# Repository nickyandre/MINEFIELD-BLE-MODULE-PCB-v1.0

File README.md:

# MINEFIELD-BLE-MODULE-PCB-v1.0
This repository is for MINEFIELD BLE Module PCB v1.0 which consist of NRF52840 BLE chip and BME280 temperature, humidity, and air pressure sensor. <br />

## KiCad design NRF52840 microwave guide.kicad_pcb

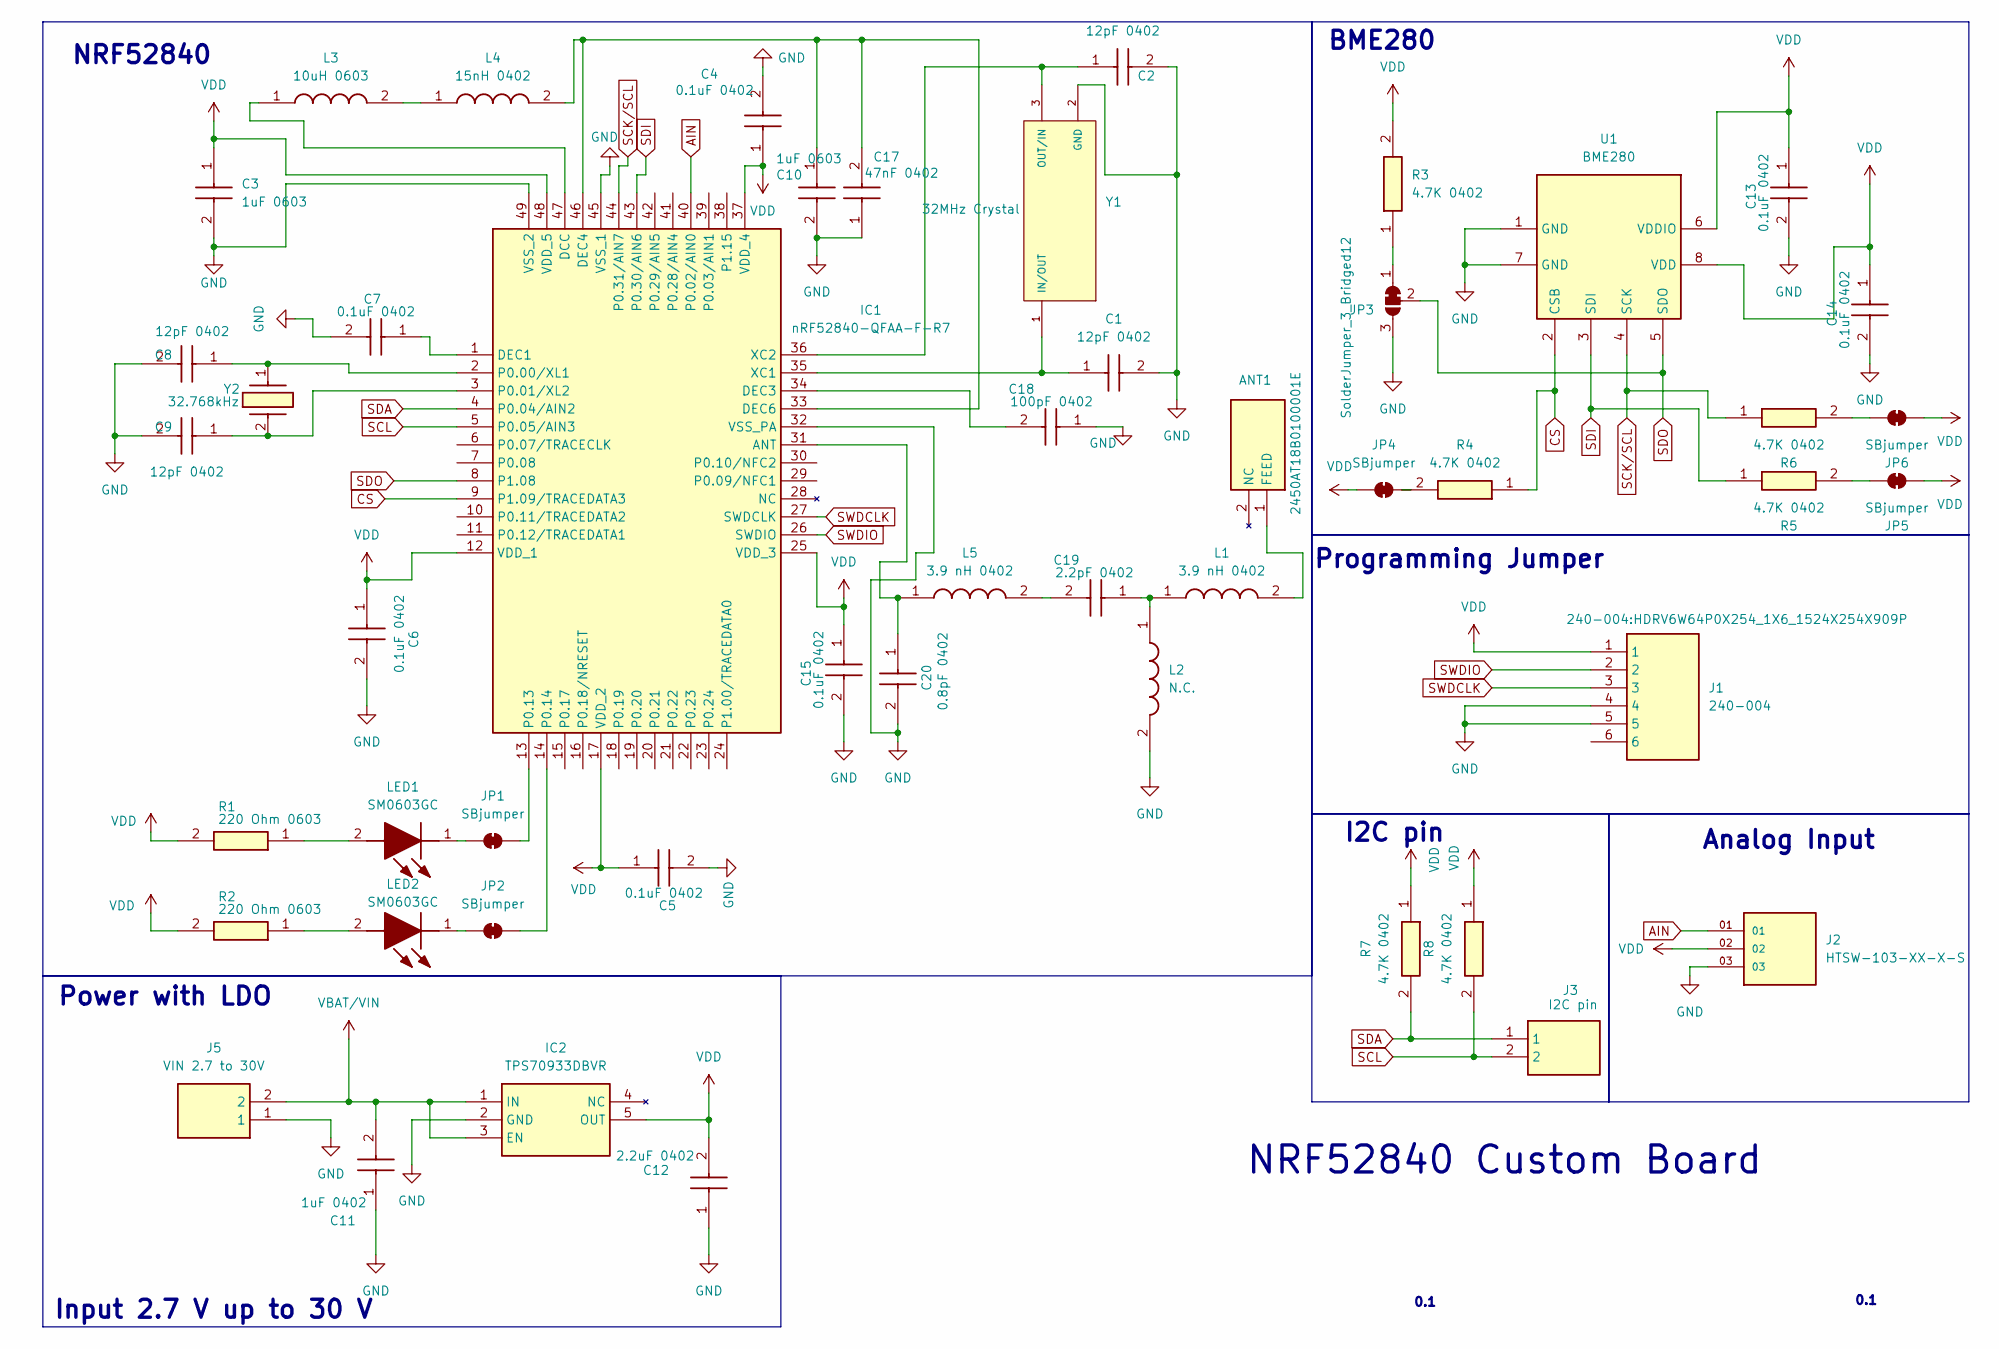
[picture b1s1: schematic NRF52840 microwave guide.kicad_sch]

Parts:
ANT1: 2450AT18B0100001E; ANTC3216X140N; Manufacturer_Part_Number 2450AT18B0100001E
C1, C2, C8, C9: 12pF 0402; 0402cap; Mouser Part Number 81-GRM1555C1H120GA1J
C3, C10: 1uF 0603; CAPC1608X90N; Manufacturer_Part_Number 06035C4R7KAT2A
C4, C5, C6, C7, C13, C14, C15: 0.1uF 0402; 0402cap; Mouser Part Number 81-GRM1555C1H120GA1J
C11: 1uF 0402; 0402cap; Mouser Part Number 81-GRM1555C1H120GA1J
C12: 2.2uF 0402; 0402cap; Mouser Part Number 81-GRM1555C1H120GA1J
C17: 47nF 0402; 0402cap; Mouser Part Number 81-GRM1555C1H120GA1J
C18: 100pF 0402; 0402cap; Mouser Part Number 81-GRM1555C1H120GA1J
C19: 2.2pF 0402; 0402cap; Mouser Part Number 81-GRM1555C1H120GA1J
C20: 0.8pF 0402; 0402cap; Mouser Part Number 81-GRM1555C1H120GA1J
IC1: nRF52840-QFAA-F-R7; QFN40P600X600X95-49N-D; Mouser Part Number 949-NRF52840QFAAF-R7
IC2: TPS70933DBVR; SOT95P280X145-5N; Mouser Part Number 595-TPS70933DBVR
J1: 240-004; HDRV6W64P0X254_1X6_1524X254X909P; Manufacturer_Part_Number 240-004
J2: HTSW-103-XX-X-S; SAMTEC_HTSW-103-XX-X-S; PARTREV B
J3: I2C pin; HDRV2W64P0X254_1X2_508X248X838P; Mouser Part Number 200-HTSW10208GS
J5: VIN 2.7 to 30V; HDRV2W64P0X254_1X2_508X248X838P; Mouser Part Number 200-HTSW10208GS
JP1, JP2, JP4, JP5, JP6: SBjumper; SolderJumper-2_P1.3mm_Bridged_RoundedPad1.0x1.5mm
JP3: SolderJumper_3_Bridged12; SolderJumper-3_P1.3mm_Bridged12_RoundedPad1.0x1.5mm_NumberL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
L1, L5: 3.9 nH 0402; MLG1005; Manufacturer_Part_Number MLG1005S3N9STD25
L2: N.C.; MLG1005; Manufacturer_Part_Number MLG1005S3N9STD25
L3: 10uH 0603; INDC1608X95N; Mouser Part Number 815-ASMCI-0603-100MT
L4: 15nH 0402; INDC1006X65N; Mouser Part Number 815-AIMC-0402Q-15NJT
LED1, LED2: SM0603GC; LEDC1608X30N; Mouser Part Number 749-SM0603GC
R1, R2: 220 Ohm 0603; RESC1608X55N; Manufacturer_Part_Number MCT06030C2219FP500; Mouser Part Number 594-MCT06030C2219FP5
R3, R4, R5, R6, R7, R8: 4.7K 0402; ERA2V__0402_; Manufacturer_Part_Number ERA-2VRW4701X
U1: BME280; Bosch_LGA-8_2.5x2.5mm_P0.65mm_ClockwisePinNumbering
Y1: 32MHz Crystal; XTAL_ECS-320-8-37BQ-CKY-TR; PARTREV 2017
Y2: 32.768kHz; CC7VT1A; Mouser Part Number 428-200039-MG01

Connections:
AIN: IC1.40 (P0.02/AIN0), J2.01
CS: IC1.9 (P1.09/TRACEDATA3), R4.1, U1.2 (CSB)
GND: C1.2, C2.2, C3.2, C4.2, C5.2, C6.2, C7.2, C8.2, C9.2, C10.2, C11.1, C12.1, C13.2, C14.2, C15.2, C17.1, C18.1, C20.2, IC1.32 (VSS_PA), IC1.45 (VSS_1), IC1.49 (VSS_2), IC2.2 (GND), J1.4, J1.5, J2.03, J5.1, JP3.3 (B), L2.2, U1.1 (GND), U1.7 (GND), Y1.2 (GND), Y1.4 (GND)
unnamed: ANT1.1 (FEED), L1.2
unnamed: C19.1, L1.1, L2.1
unnamed: C19.2, L5.2
unnamed: C20.1, IC1.31 (ANT), L5.1
unnamed: IC1.47 (DCC), L3.1
unnamed: C7.1, IC1.1 (DEC1)
unnamed: C18.2, IC1.34 (DEC3)
unnamed: C10.1, C17.2, IC1.33 (DEC6), IC1.46 (DEC4), L4.2
unnamed: C8.1, IC1.2 (P0.00/XL1), Y2.1
unnamed: C9.1, IC1.3 (P0.01/XL2), Y2.2 (X2)
unnamed: IC1.13 (P0.13), JP1.2 (B)
unnamed: IC1.14 (P0.14), JP2.2 (B)
unnamed: C1.1, IC1.35 (XC1), Y1.1 (IN/OUT)
unnamed: C2.1, IC1.36 (XC2), Y1.3 (OUT/IN)
unnamed: JP1.1 (A), LED1.1 (K)
unnamed: JP2.1 (A), LED2.1 (K)
unnamed: JP3.1 (A), R3.1
unnamed: JP4.2 (B), R4.2
unnamed: JP5.2 (B), R5.2
unnamed: JP6.2 (B), R6.2
unnamed: L3.2, L4.1
unnamed: LED1.2 (A), R1.1
unnamed: LED2.2 (A), R2.1
SCK/SCL: IC1.44 (P0.31/AIN7), R6.1, U1.4 (SCK)
SCL: IC1.5 (P0.05/AIN3), J3.2, R8.2
SDA: IC1.4 (P0.04/AIN2), J3.1, R7.2
SDI: IC1.43 (P0.30/AIN6), R5.1, U1.3 (SDI)
SDO: IC1.8 (P1.08), JP3.2 (C), U1.5 (SDO)
SWDCLK: IC1.27 (SWDCLK), J1.3
SWDIO: IC1.26 (SWDIO), J1.2
VBAT/VIN: C11.2, IC2.1 (IN), IC2.3 (EN), J5.2
VDD: C3.1, C4.1, C5.1, C6.1, C12.2, C13.1, C14.1, C15.1, IC1.12 (VDD_1), IC1.17 (VDD_2), IC1.25 (VDD_3), IC1.37 (VDD_4), IC1.48 (VDD_5), IC2.5 (OUT), J1.1, J2.02, JP4.1 (A), JP5.1 (A), JP6.1 (A), R1.2, R2.2, R3.2, R7.1, R8.1, U1.6 (VDDIO), U1.8 (VDD)

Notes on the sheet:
Programming Jumper
NRF52840
0.1
BME280
NRF52840 Custom Board
I2C pin
Input 2.7 V up to 30 V
Power with LDO
Analog Input

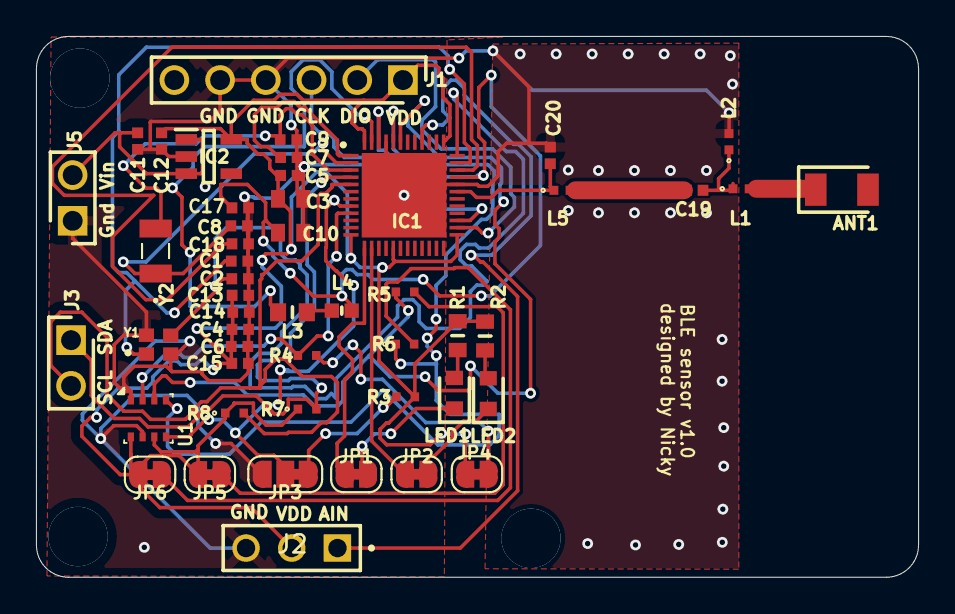
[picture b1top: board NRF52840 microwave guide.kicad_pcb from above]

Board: 2 copper layers, 49.0 x 30.0 mm, 50 parts (0 on the bottom side), 35 nets.

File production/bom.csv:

Designator,Footprint,Quantity,Value,LCSC Part #
ANT1,ANTC3216X140N,1,2450AT18B0100001E,
"C1, C2, C8, C9",0402cap,4,12pF 0402,
"C10, C3",CAPC1608X90N,2,1uF 0603,
C11,0402cap,1,1uF 0402,
C12,0402cap,1,2.2uF 0402,
"C13, C14, C15, C4, C5, C6, C7",0402cap,7,0.1uF 0402,
C17,0402cap,1,47nF 0402,
C18,0402cap,1,100pF 0402,
C19,0402cap,1,2.2pF 0402,
C20,0402cap,1,0.8pF 0402,
IC1,QFN40P600X600X95-49N-D,1,nRF52840-QFAA-F-R7,
IC2,SOT95P280X145-5N,1,TPS70933DBVR,
J1,HDRV6W64P0X254_1X6_1524X254X909P,1,240-004,
J2,SAMTEC_HTSW-103-XX-X-S,1,HTSW-103-XX-X-S,
J3,HDRV2W64P0X254_1X2_508X248X838P,1,I2C pin,
J5,HDRV2W64P0X254_1X2_508X248X838P,1,VIN 2.7 to 30V,
"L1, L5",MLG1005,2,3.9 nH 0402,
L2,MLG1005,1,N.C.,
L3,INDC1608X95N,1,10uH 0603,
L4,INDC1006X65N,1,15nH 0402,
"LED1, LED2",LEDC1608X30N,2,SM0603GC,
"R1, R2",RESC1608X55N,2,220 Ohm 0603,
"R3, R4, R5, R6, R7, R8",ERA2V__0402_,6,4.7K 0402,
U1,Bosch_LGA-8_2.5x2.5mm_P0.65mm_ClockwisePinNumbering,1,BME280,
Y1,XTAL_ECS-320-8-37BQ-CKY-TR,1,32MHz Crystal,
Y2,CC7VT1A,1,32.768kHz,
